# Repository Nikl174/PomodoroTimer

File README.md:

# Pomodoro Timer

A little USB A timer user for the [Pomdoro Technique](https://en.wikipedia.org/wiki/Pomodoro_Technique).

## Features

- small and powerful ATTiny412 as MCU
- 12 WS2813B RGB LEDs
- 3 Buttons
- I2C Header for playing around
- power over USB C or integrated USB A connector

## Structure

`pcb/`
: KiCAD Files for the electronic schematics and the routed layout

`code/`
: Arduino Code for a simple implementation of the pomodoro technique

`housing/`
: FreeCAD Model for a simple housing for the board

`doc/`
: Datasheets

## Dependencies

### Hardware

- [Components Library](https://gitlab.fabcloud.org/pub/libraries/electronics/kicad) - Component library used for the PCB
- [Serial D11C Programmer](https://gitlab.fabcloud.org/pub/programmers/programmer-serial-d11c) - UPDI Programmer used for flashing together with this [adapter](https://leomcelroy.com/svg-pcb/?file=hello.serial-UPDI.3.js), but also possible with e.g.:
    - [SWD+UART Board](https://gitlab.fabcloud.org/pub/programmers/swd-uart-adapter-xiao-rp2040)
    - [UPDI D11C](https://gitlab.fabcloud.org/pub/programmers/programmer-updi-d11c)
- [MegaTinyCore](https://github.com/SpenceKonde/megaTinyCore/) - arduino library used for programming the ATTiny412
- an arduino environment, more in [here](/code/README.md)
- [KiCAD](https://www.kicad.org/) for editing the PCB/ creating other production files
- [FreeCAD](https://www.freecad.org/) for editing the housing

## BOM Components

| Designator                              | Footprint                                   | Quantity | Designation                 |
|-----------------------------------------|---------------------------------------------|----------|-----------------------------|
| U6,U8,U3,U9,U11,U10,U2,U12,U4,U7,U5,U13 | LED_ADDR_Worldsemi_WS2812B                  | 12       | WS2812B                     |
| R2,R7                                   | R_1206                                      | 2        | 0R                          |
| J2                                      | PinHeader_01x04_P2.54mm_Vertical_THT_D1.4mm | 1        | I2C Header                  |
| P1                                      | Conn_USB_A_Plain                            | 1        | Conn_USB_A_Plain            |
| C3                                      | C_1206                                      | 1        | 100nF                       |
| R3                                      | R_1206                                      | 1        | 100R                        |
| SW3                                     | Button_Omron_B3SN_6.0x6.0mm                 | 1        | Restart                     |
| R6,R1                                   | R_1206                                      | 2        | 1kR                         |
| D4                                      | LED_1206                                    | 1        | Power LED                   |
| SW1                                     | Button_Omron_B3SN_6.0x6.0mm                 | 1        | Start/Stop                  |
| U1                                      | SOIC-8_3.9x4.9mm_P1.27mm                    | 1        | ATtiny412                   |
| J1                                      | PinHeader_01x03_P2.54mm_Vertical_THT_D1.4mm | 1        | UPDI Flash Header           |
| J3                                      | Conn_USB_C_Socket_GCT_USB4125-GF-A-0190     | 1        | Conn_USB_C_Socket_PowerOnly |
| R5                                      | R_1206                                      | 1        | 499R                        |
| SW2                                     | Button_Omron_B3SN_6.0x6.0mm                 | 1        | Skip                        |

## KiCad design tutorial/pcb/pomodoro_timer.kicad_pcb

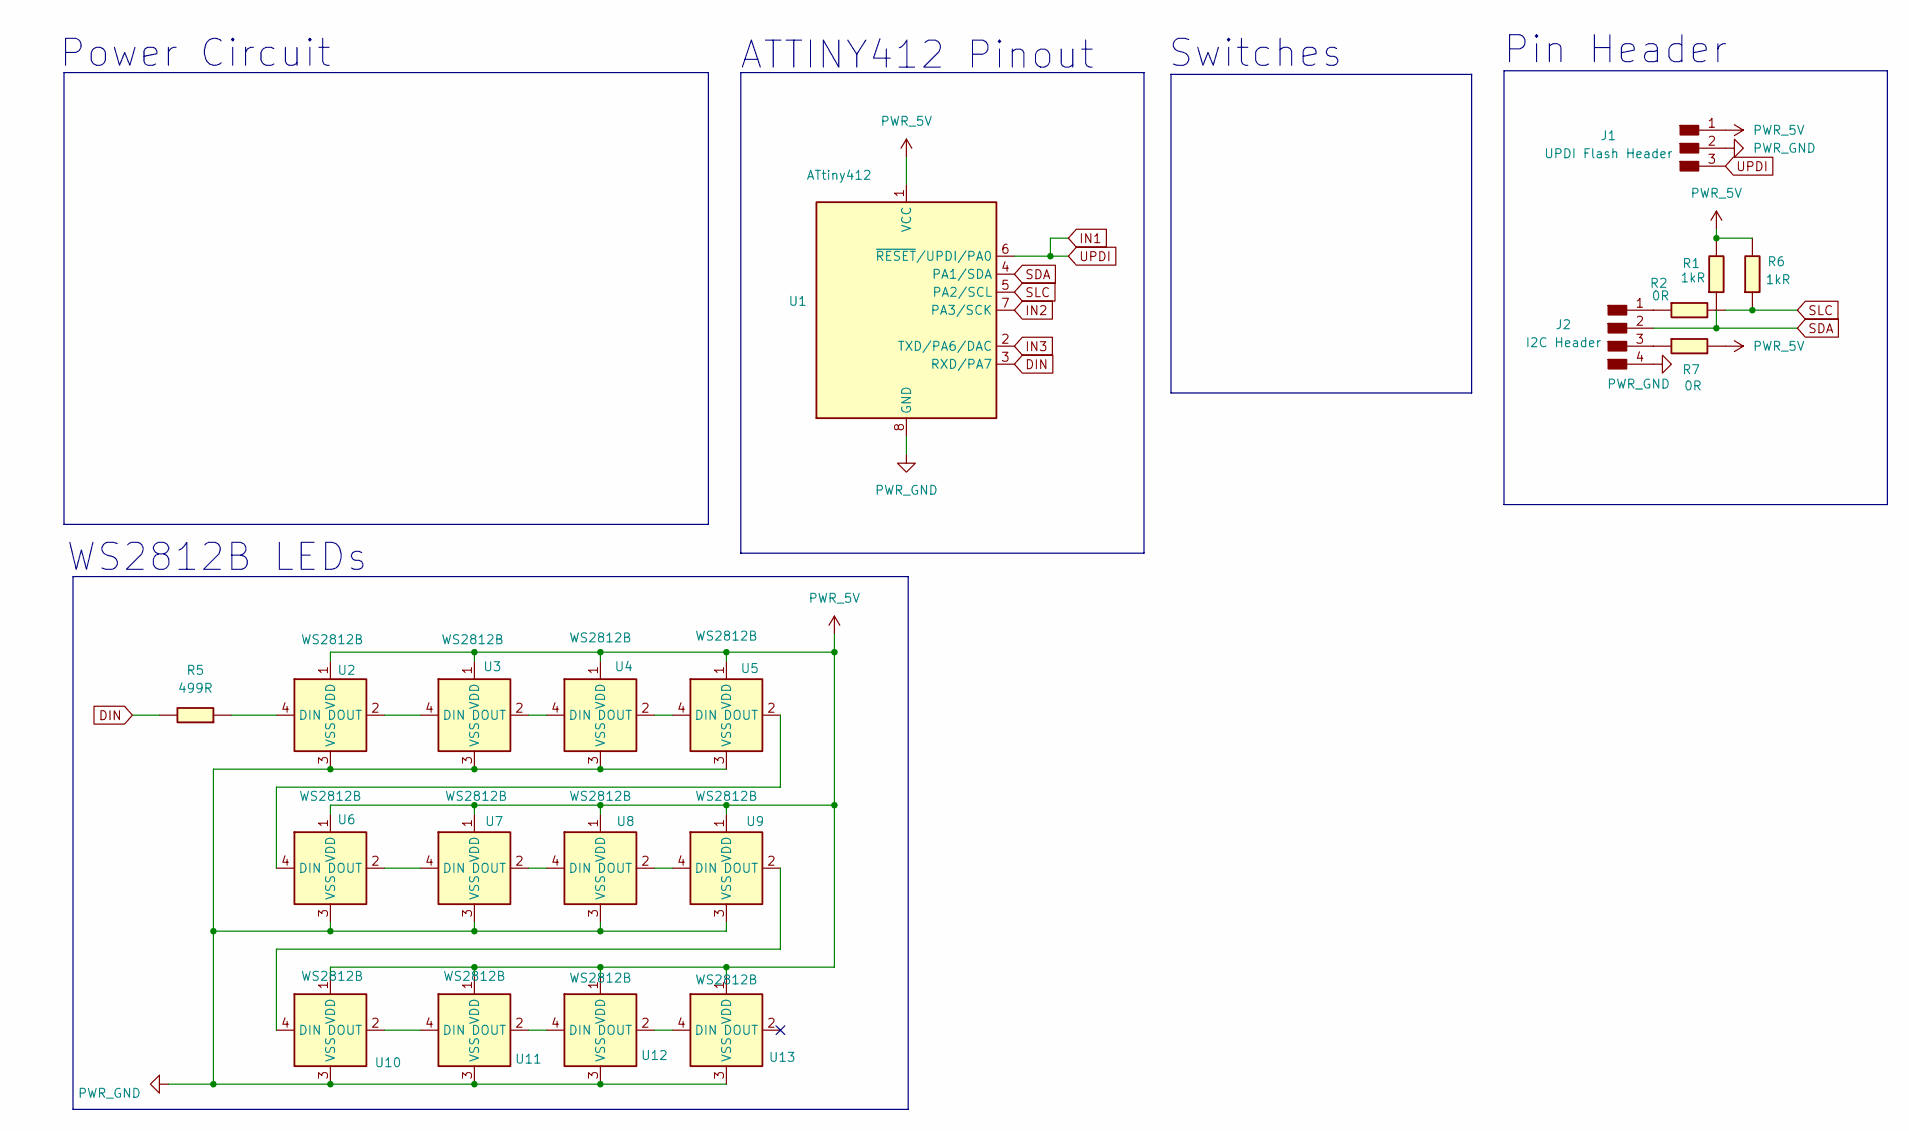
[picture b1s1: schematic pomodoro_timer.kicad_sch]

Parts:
J1: UPDI Flash Header; PinHeader_01x03_P2.54mm_Vertical_THT_D1.4mm
J2: I2C Header; PinHeader_01x04_P2.54mm_Vertical_THT_D1.4mm
R1, R6: 1kR; R_1206
R2, R7: 0R; R_1206
R5: 499R; R_1206
U1: ATtiny412; SOIC-8_3.9x4.9mm_P1.27mm
U2, U3, U4, U5, U6, U7, U8, U9, U10, U11, U12, U13: WS2812B; LED_ADDR_Worldsemi_WS2812B

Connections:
DIN: R5.1, U1.3 (RXD/PA7)
IN1: J1.3, U1.6 (~RESET/UPDI/PA0)
IN2: U1.7 (PA3/SCK)
IN3: U1.2 (TXD/PA6/DAC)
unnamed: J2.1, R2.2
unnamed: J2.3, R7.2
unnamed: R5.2, U2.4 (DIN)
unnamed: U2.2 (DOUT), U3.4 (DIN)
unnamed: U3.2 (DOUT), U4.4 (DIN)
unnamed: U4.2 (DOUT), U5.4 (DIN)
unnamed: U5.2 (DOUT), U6.4 (DIN)
unnamed: U6.2 (DOUT), U7.4 (DIN)
unnamed: U7.2 (DOUT), U8.4 (DIN)
unnamed: U8.2 (DOUT), U9.4 (DIN)
unnamed: U9.2 (DOUT), U10.4 (DIN)
unnamed: U10.2 (DOUT), U11.4 (DIN)
unnamed: U11.2 (DOUT), U12.4 (DIN)
unnamed: U12.2 (DOUT), U13.4 (DIN)
PWR_5V: J1.1, R1.1, R6.1, R7.1, U1.1 (VCC), U2.1 (VDD), U3.1 (VDD), U4.1 (VDD), U5.1 (VDD), U6.1 (VDD), U7.1 (VDD), U8.1 (VDD), U9.1 (VDD), U10.1 (VDD), U11.1 (VDD), U12.1 (VDD), U13.1 (VDD); also elsewhere on the board
PWR_GND: J1.2, J2.4, U1.8 (GND), U2.3 (VSS), U3.3 (VSS), U4.3 (VSS), U5.3 (VSS), U6.3 (VSS), U7.3 (VSS), U8.3 (VSS), U9.3 (VSS), U10.3 (VSS), U11.3 (VSS), U12.3 (VSS), U13.3 (VSS); also elsewhere on the board
SDA: J2.2, R1.2, U1.4 (PA1/SDA)
SLC: R2.1, R6.2, U1.5 (PA2/SCL)

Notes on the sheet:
Pin Header
Power Circuit
ATTINY412 Pinout
WS2812B LEDs
Switches

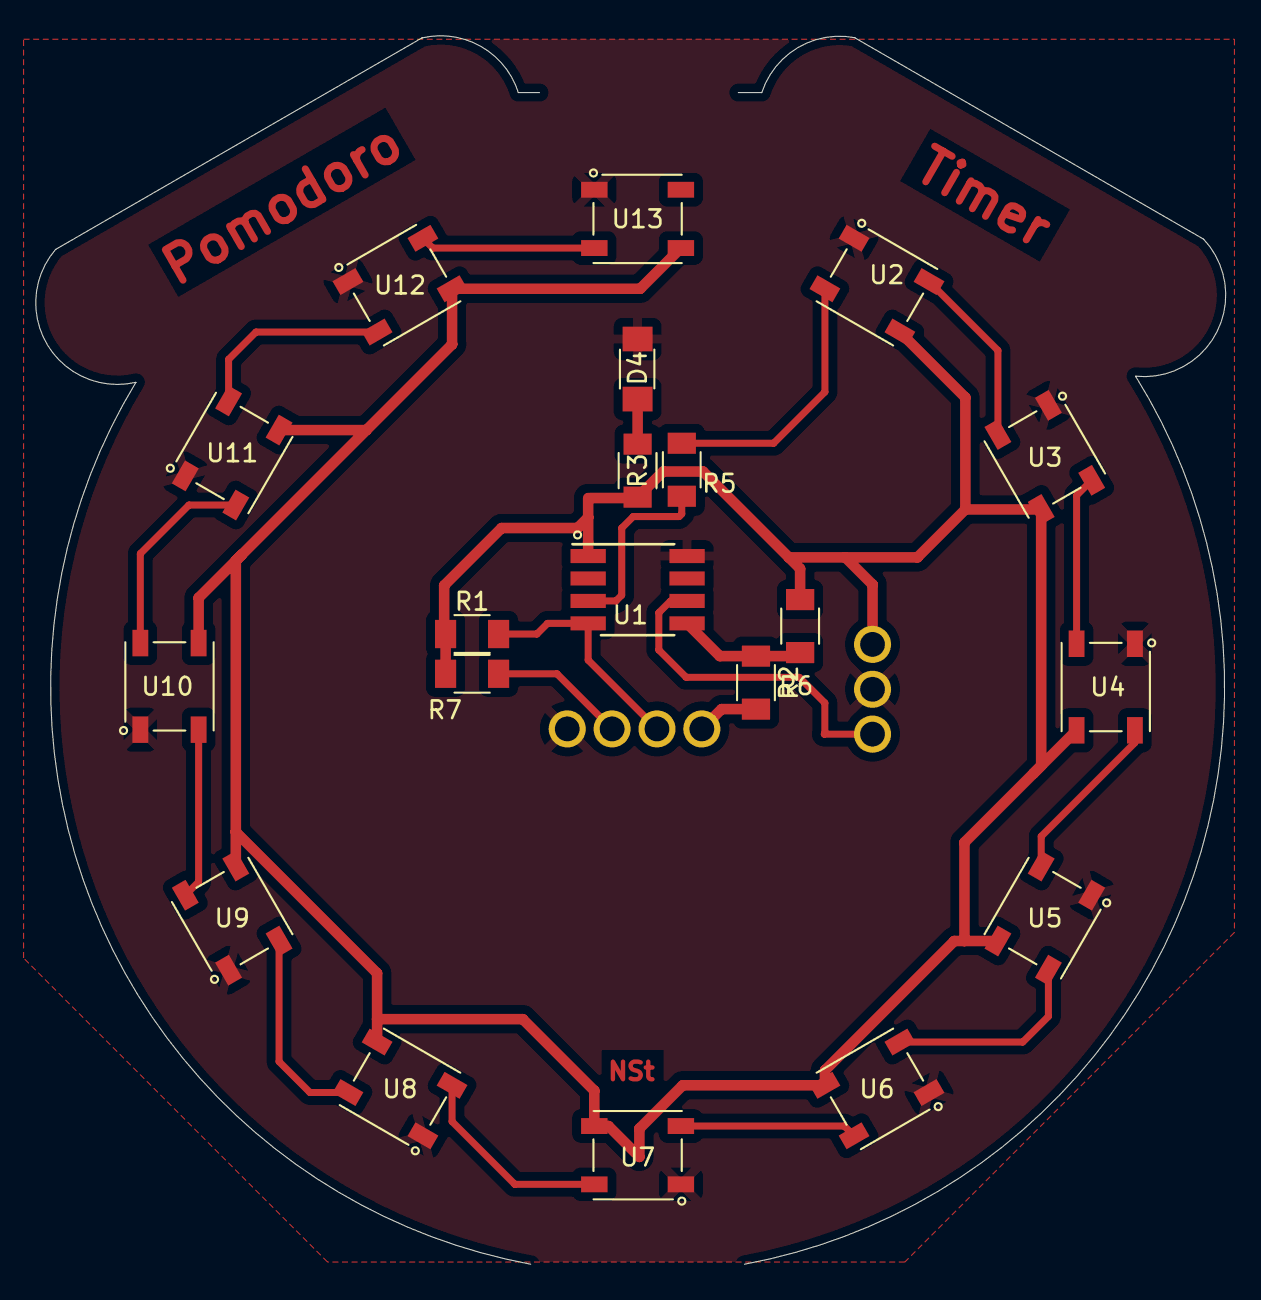
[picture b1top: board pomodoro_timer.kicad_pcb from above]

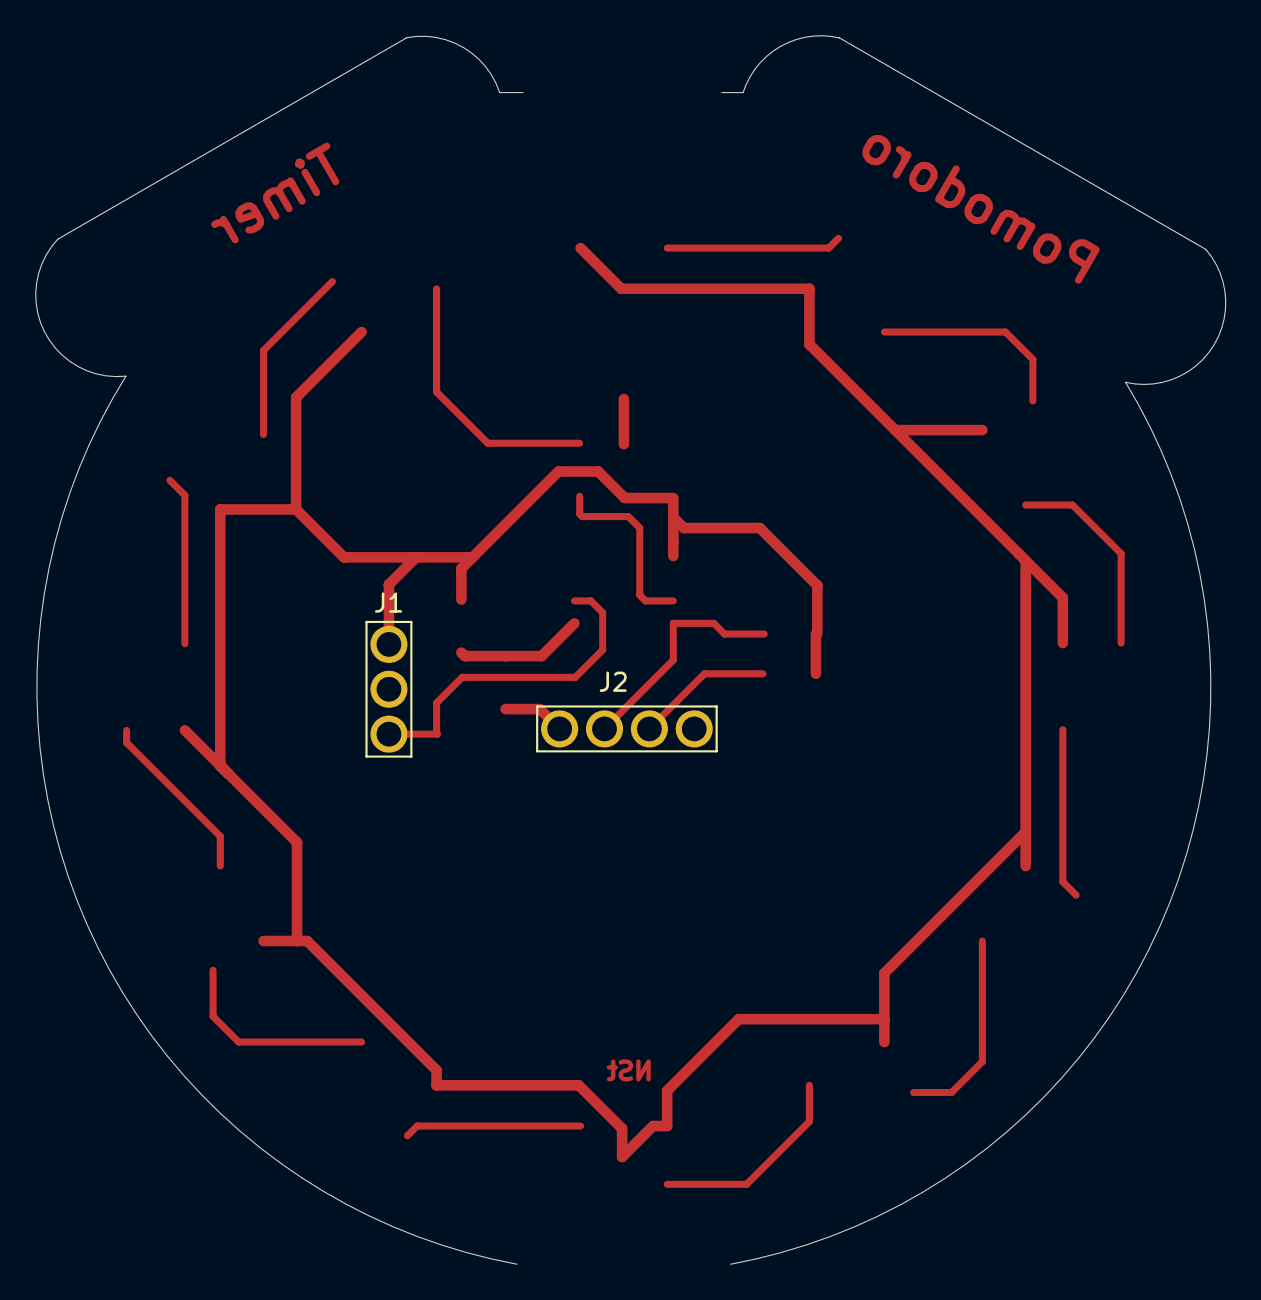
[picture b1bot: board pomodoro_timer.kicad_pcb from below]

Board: 2 copper layers, 67.4 x 69.5 mm, 22 parts (2 on the bottom side), 21 nets.

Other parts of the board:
D4: Power LED; LED_1206
R3: 100R; R_1206

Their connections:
unnamed: D4.2 (A), R3.1
PWR_5V: R3.2; also elsewhere on the board
PWR_GND: D4.1 (K); also elsewhere on the board

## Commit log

2025-09-22 added housing for PCB
2025-09-22 added code for simple pomodoro-timer in arduino + uml state diagramm
2025-09-22 removed old code
2025-09-22 PCB: updated schematics and routing
2025-09-22 added production files
2025-09-22 moved pcb files to other directory
2025-09-22 added project README
2025-09-22 updated image
2025-09-22 updated README, added KiCAD tutorial Project, improved gitignores
2025-09-22 Fixed filename and added doc
2025-09-25 code: fixed error: state change and added pause brightness change
2025-09-25 housing: improved clamps
2025-09-25 code: added documentation
2025-09-25 code: improved doc
2025-09-25 removed tutorial files
2025-09-25 code: improved doc and added interrupt implementation
2025-09-25 added documentation pdfs
2026-02-15 added more description with quentores flasher
2026-02-15 fixed typo
